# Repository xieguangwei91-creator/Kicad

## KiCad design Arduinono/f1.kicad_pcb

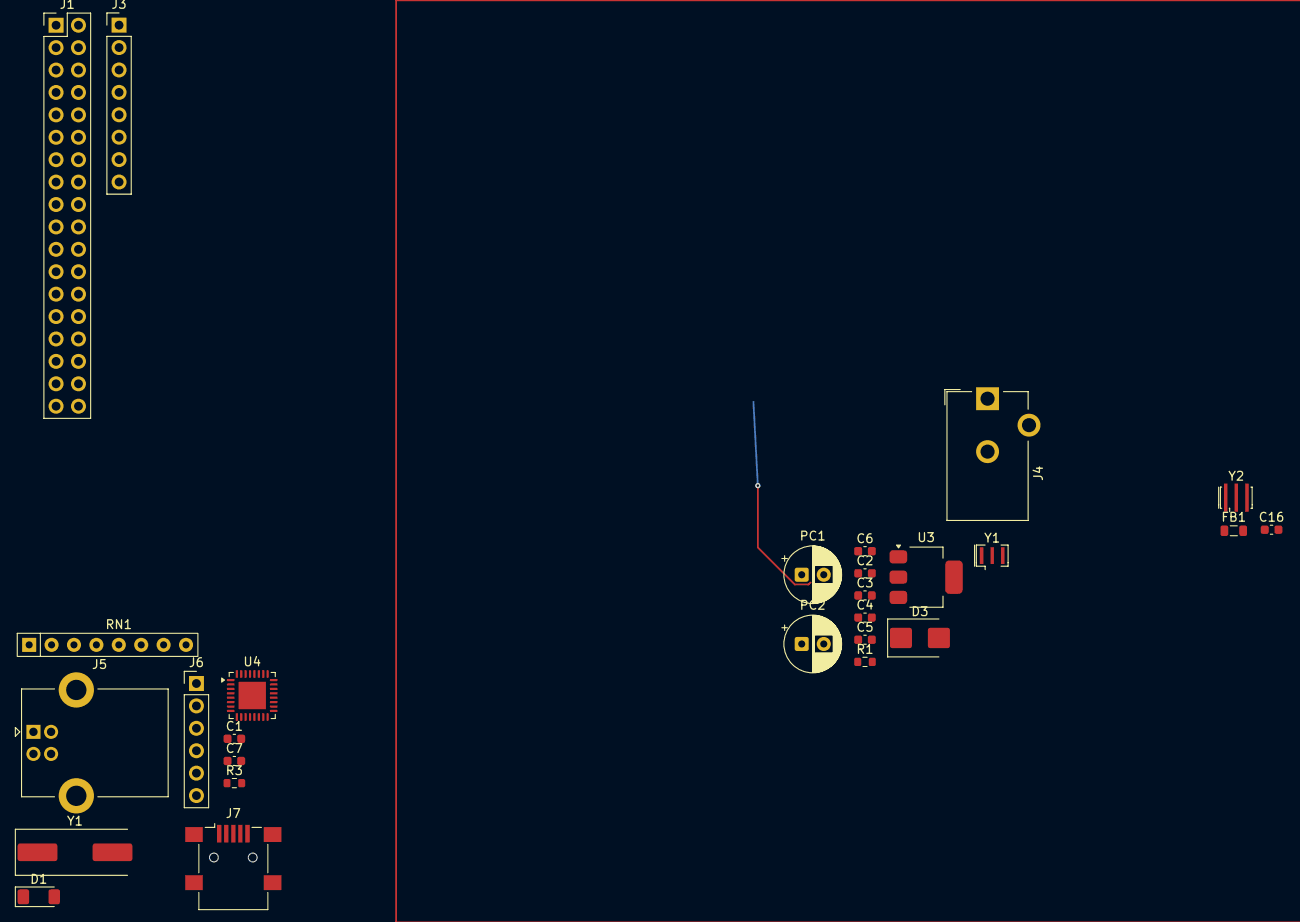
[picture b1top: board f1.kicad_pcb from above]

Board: 2 copper layers, 28 parts (1 on the bottom side), 13 nets.

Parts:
C1, C2, C4, C5, C6, C7, C16: C; C_0603_1608Metric
C3: 100nF; C_0603_1608Metric
D1: D; D_MiniMELF
D3: D; D_SMB
FB1: FerriteBead; L_0805_2012Metric
J1: Conn_02x18_Counter_Clockwise; PinHeader_2x18_P2.54mm_Vertical
J3: Conn_01x08_Socket; PinHeader_1x08_P2.54mm_Vertical
J4: Barrel_Jack_Switch; BarrelJack_CUI_PJ-102AH_Horizontal
J5: USB_B; USB_B_Lumberg_2411_02_Horizontal
J6: Conn_PIC_ICSP_ICD; PinHeader_1x06_P2.54mm_Vertical
J7: USB_B_Mini; USB_Mini-B_Lumberg_2486_01_Horizontal
PC1, PC2: C_Polarized; CP_Radial_D6.3mm_P2.50mm
R1, R3: R; R_0603_1608Metric
RN1: R_Pack04_SIP_Split; R_Array_SIP8
U1: ATmega2560-16A; TQFP-100_14x14mm_P0.5mm
U3: LD1117S50TR_SOT223; SOT-223-3_TabPin2
U4: ATmega16U2-M; QFN-32-1EP_5x5mm_P0.5mm_EP3.1x3.1mm
Y1: Resonator; Resonator_SMD_Murata_CSTxExxV-3Pin_3.0x1.1mm
Y1#2: Crystal_Small; Crystal_SMD_HC49-SD
Y2: Resonator; Resonator_SMD_Murata_CSTxExxV-3Pin_3.0x1.1mm_HandSoldering

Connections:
5V: C4.1, C5.1, C6.1, D1.1 (K), FB1.2, J1.1, J1.2, J3.2, J3.5, PC2.1, RN1.2 (R1.2), U3.2 (VO)
/<NO NET>: C2.1, D3.1 (K), J3.8, PC1.1, U3.3 (VI)
/RESET2: D1.2 (A), RN1.1 (R1.1), U4.24 (PC1/~RESET)
GND: C1.1, C2.2, C3.2, C4.2, C5.2, C6.2, C7.1, C16.2, J1.35, J1.36, J3.6, J3.7, J4.2, J4.3, PC1.2, PC2.2, U3.1 (GND), Y1.2, Y2.2
unnamed: C16.1, FB1.1
unnamed: D3.2 (A), J4.1
unnamed: R1.1, Y1.1, Y2.1
unnamed: R1.2, Y1.3, Y2.3
unnamed: U1.11 (GND), U1.32 (GND), U1.62 (GND), U1.81 (GND), U1.99 (GND)
unnamed: U1.10 (VCC), U1.31 (VCC), U1.61 (VCC), U1.80 (VCC)
unnamed: U4.3 (GND), U4.33 (GND)
unnamed: C7.2, R3.2, U4.2 (PC0/XTAL2), Y1#2.1
unnamed: C1.2, R3.1, U4.1 (XTAL1), Y1#2.2

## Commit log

2026-04-17 Create Arrdduuiinnoo
